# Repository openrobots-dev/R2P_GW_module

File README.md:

R2P GW module
===================

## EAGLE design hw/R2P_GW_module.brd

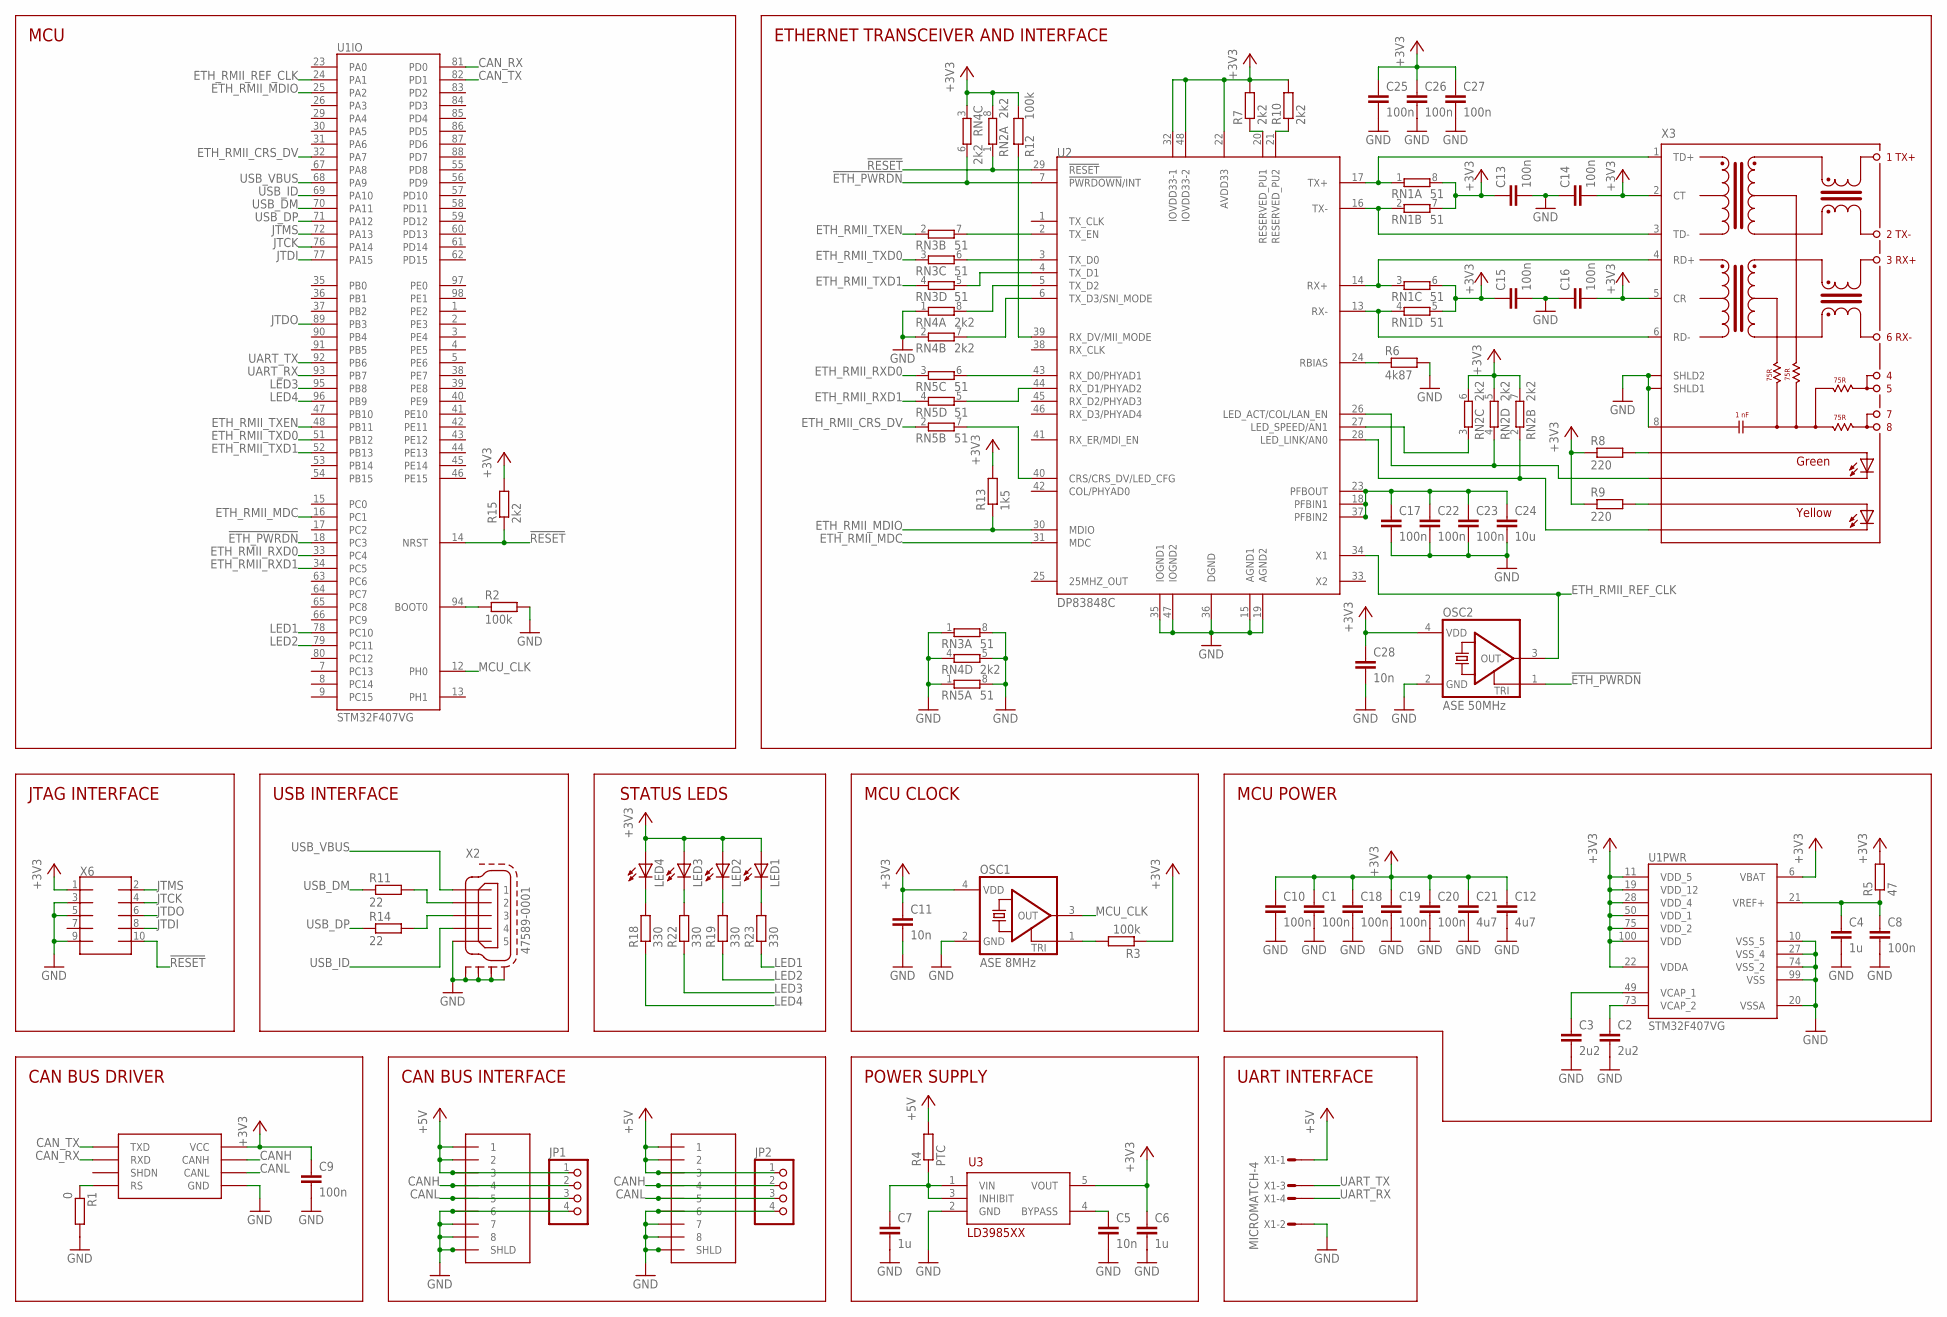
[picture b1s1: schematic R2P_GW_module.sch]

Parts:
C1, C8, C9, C10, C13, C14, C15, C16, C17, C18, C19, C20, C22, C23, C25, C26, C27: 100n; C0603
C2, C3: 2u2; C0805
C4, C6, C7: 1u; C0603
C5, C11, C28: 10n; C0603
C12, C21: 4u7; C0805
C24: 10u; C0805
JP1, JP2: PINHD-1X4; 1X04
LED1, LED2, LED3, LED4: LEDCHIPLED_0805; CHIPLED_0805
OSC1: ASE 8MHz; ASE
OSC2: ASE 50MHz; ASE
R1: 0; R0603
R2, R3, R12: 100k; R0603
R4: PTC; R0603
R5: 47; R0603
R6: 4k87; R0603
R7, R10, R15: 2k2; R0603
R8, R9: 220; R0603
R11, R14: 22; R0603
R13: 1k5; R0603
R18, R19, R22, R23: 330; R0603
RN1, RN3, RN5: 51; CAT16
RN2, RN4: 2k2; CAT16
U1: STM32F407VG; LQFP100
U2: DP83848C; LQFP48
U3: LD3985XX; SOT23-5L
U4: MAX3051; SOT23-8L
X1: MICROMATCH-4
X2: 47589-0001
X3: SI-60062-F
X4, X5: RJ45-43860; 0438600010
X6: FTSH-105

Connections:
!ETH_PWRDN: OSC2.1 (TRI), RN4.6 (2), U1.18 (PC3), U2.7 (!PWRDOWN!/INT)
!RESET: R15.1, RN2.1, U1.14 (NRST), U2.29 (!RESET), X6.10
+3V3: C1.1, C6.1, C9.1, C10.1, C11.1, C12.1, C13.1, C14.2, C15.1, C16.2, C18.1, C19.1, C20.1, C21.1, C25.1, C26.1, C27.1, C28.1, LED1.A, LED2.A, LED3.A, LED4.A, OSC1.4 (VDD), OSC2.4 (VDD), R3.1, R5.2, R7.2, R8.1, R9.1, R10.2, R12.2, R13.2, R15.2, RN1.5 (2), RN1.6 (2), RN1.7 (2), RN1.8 (2), RN2.5 (2), RN2.6 (2), RN2.7 (2), RN2.8 (2), RN4.3 (1), U1.6 (VBAT), U1.11 (VDD_5), U1.19 (VDD_12), U1.22 (VDDA), U1.28 (VDD_4), U1.50 (VDD_1), U1.75 (VDD_2), U1.100 (VDD), U2.22 (AVDD33), U2.32 (IOVDD33-1), U2.48 (IOVDD33-2), U3.5 (VOUT), U4.P$3 (VCC), X3.2 (CT), X3.5 (CR), X6.1
+5V: JP1.1, JP2.1, R4.2, X1.1, X4.P$1 (1), X4.P$2 (2), X4.P$3 (3), X5.P$1 (1), X5.P$2 (2), X5.P$3 (3)
CANH: JP1.2, JP2.2, U4.P$7 (CANH), X4.P$4 (4), X5.P$4 (4)
CANL: JP1.3, JP2.3, U4.P$6 (CANL), X4.P$5 (5), X5.P$5 (5)
CAN_RX: U1.81 (PD0), U4.P$4 (RXD)
CAN_TX: U1.82 (PD1), U4.P$1 (TXD)
ETH_RMII_CRS_DV: RN5.2 (1), U1.32 (PA7)
ETH_RMII_MDC: U1.16 (PC1), U2.31 (MDC)
ETH_RMII_MDIO: R13.1, U1.25 (PA2), U2.30 (MDIO)
ETH_RMII_REF_CLK: OSC2.3 (OUT), U1.24 (PA1), U2.34 (X1)
ETH_RMII_RXD0: RN5.3 (1), U1.33 (PC4)
ETH_RMII_RXD1: RN5.4 (1), U1.34 (PC5)
ETH_RMII_TXD0: RN3.3 (1), U1.51 (PB12)
ETH_RMII_TXD1: RN3.4 (1), U1.52 (PB13)
ETH_RMII_TXEN: RN3.2 (1), U1.48 (PB11)
GND: C1.2, C2.2, C3.2, C4.2, C5.2, C6.2, C7.2, C8.2, C9.2, C10.2, C11.2, C12.2, C13.2, C14.1, C15.2, C16.1, C17.2, C18.2, C19.2, C20.2, C21.2, C22.2, C23.2, C24.2, C25.2, C26.2, C27.2, C28.2, JP1.4, JP2.4, OSC1.2 (GND), OSC2.2 (GND), R1.2, R2.2, R6.2, RN3.1, RN3.8 (2), RN4.1, RN4.2 (1), RN4.4 (1), RN4.5 (2), RN5.1, RN5.8 (2), U1.10 (VSS_5), U1.20 (VSSA), U1.27 (VSS_4), U1.74 (VSS_2), U1.99 (VSS), U2.15 (AGND1), U2.19 (AGND2), U2.35 (IOGND1), U2.36 (DGND), U2.47 (IOGND2), U3.2 (GND), U4.P$2 (GND), X1.2, X2.5, X2.SHLD1, X2.SHLD2, X2.SHLD3, X2.SHLD4, X3.8, X3.SHLD1, X3.SHLD2, X4.P$6 (6), X4.P$7 (7), X4.P$8 (8), X4.P$9 (SHLD), X4.P$10, X5.P$6 (6), X5.P$7 (7), X5.P$8 (8), X5.P$9 (SHLD), X5.P$10, X6.3, X6.5, X6.9
JTCK: U1.76 (PA14), X6.4
JTDI: U1.77 (PA15), X6.8
JTDO: U1.89 (PB3), X6.6
JTMS: U1.72 (PA13), X6.2
LED1: R23.1, U1.78 (PC10)
LED2: R19.1, U1.79 (PC11)
LED3: R22.1, U1.95 (PB8)
LED4: R18.1, U1.96 (PB9)
MCU_CLK: OSC1.3 (OUT), U1.12 (PH0)
unnamed: C4.1, C8.1, R5.1, U1.21 (VREF+)
unnamed: R1.1, U4.P$8 (RS)
unnamed: OSC1.1 (TRI), R3.2
unnamed: C5.1, U3.4 (BYPASS)
unnamed: C7.1, R4.1, U3.1 (VIN), U3.3 (INHIBIT)
unnamed: R6.1, U2.24 (RBIAS)
unnamed: R11.2, X2.2
unnamed: RN1.1, U2.17 (TX+), X3.1 (TD+)
unnamed: RN1.2 (1), U2.16 (TX-), X3.3 (TD-)
unnamed: RN1.3 (1), U2.14 (RX+), X3.4 (RD+)
unnamed: RN1.4 (1), U2.13 (RX-), X3.6 (RD-)
unnamed: R9.2, X3.YA
unnamed: C17.1, C22.1, C23.1, C24.1, U2.18 (PFBIN1), U2.23 (PFBOUT), U2.37 (PFBIN2)
unnamed: LED4.C, R18.2
unnamed: R8.2, X3.GA
unnamed: LED2.C, R19.2
unnamed: RN2.3 (1), U2.27 (LED_SPEED/AN1)
unnamed: LED3.C, R22.2
unnamed: RN3.7 (2), U2.2 (TX_EN)
unnamed: LED1.C, R23.2
unnamed: RN2.2 (1), U2.28 (LED_LINK/AN0), X3.YK
unnamed: RN2.4 (1), U2.26 (LED_ACT/COL/LAN_EN), X3.GK
unnamed: RN3.6 (2), U2.3 (TX_D0)
unnamed: R2.1, U1.94 (BOOT0)
unnamed: R7.1, U2.20 (RESERVED_PU1)
unnamed: R10.1, U2.21 (RESERVED_PU2)
unnamed: RN3.5 (2), U2.4 (TX_D1)
unnamed: RN4.8 (2), U2.5 (TX_D2)
unnamed: RN4.7 (2), U2.6 (TX_D3/SNI_MODE)
unnamed: R14.2, X2.3
unnamed: RN5.6 (2), U2.43 (RX_D0/PHYAD1)
unnamed: R12.1, U2.39 (RX_DV/MII_MODE)
unnamed: RN5.5 (2), U2.44 (RX_D1/PHYAD2)
unnamed: RN5.7 (2), U2.40 (CRS/CRS_DV/LED_CFG)
UART_RX: U1.93 (PB7), X1.4
UART_TX: U1.92 (PB6), X1.3
USB_DM: R11.1, U1.70 (PA11)
USB_DP: R14.1, U1.71 (PA12)
USB_ID: U1.69 (PA10), X2.4
USB_VBUS: U1.68 (PA9), X2.1
VCAP_1: C3.1, U1.49 (VCAP_1)
VCAP_2: C2.1, U1.73 (VCAP_2)

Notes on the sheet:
MCU
POWER SUPPLY
STATUS LEDS
JTAG INTERFACE
CAN BUS INTERFACE
CAN BUS DRIVER
UART INTERFACE
ETHERNET TRANSCEIVER AND INTERFACE
MCU POWER
MCU CLOCK
USB INTERFACE

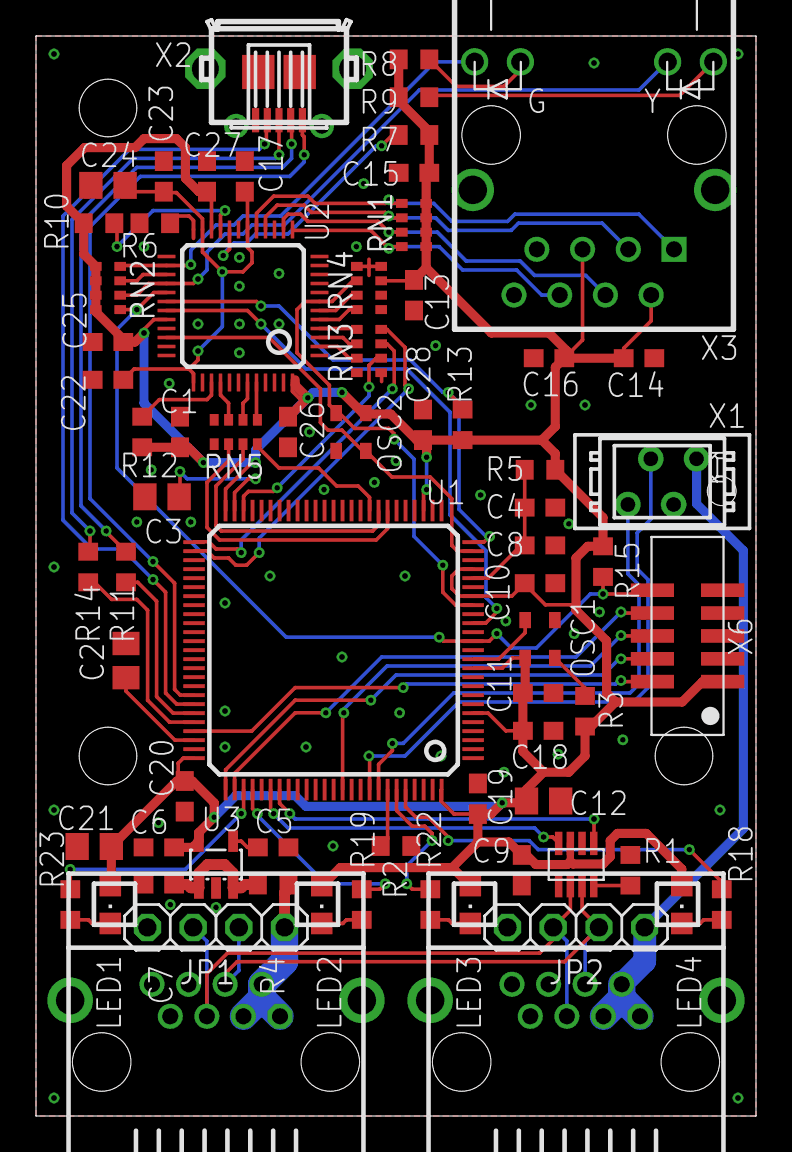
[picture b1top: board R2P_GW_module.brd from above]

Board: 2 copper layers, 40.0 x 60.0 mm, 70 parts (0 on the bottom side), 69 nets.

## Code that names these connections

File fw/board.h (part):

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/*
 * IO pins assignments.
 */
#define LED1_GPIO				GPIOC
#define LED1					10
#define LED2_GPIO				GPIOC
#define LED2					11
#define LED3_GPIO				GPIOB
#define LED3					8
#define LED4_GPIO				GPIOB
#define LED4					9

#define SERIAL_DRIVER           SD1

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 * GPIOA setup:
 *
 * PA0  - PIN0                      (input pullup).
 * PA1  - ETH_RMII_REF_CLK          (alternate 11).
 * PA2  - ETH_RMII_MDIO             (alternate 11).
 * PA3  - PIN3                      (input pullup).
 * PA4  - PIN4                      (input pullup).
 * PA5  - PIN5                      (input pullup).
 * PA6  - PIN6                      (input pullup).
 * PA7  - ETH_RMII_CRS_DV           (alternate 11).
 * PA8  - PIN8                      (input pullup).
 * PA9  - OTG_FS_VBUS               (input pulldown).
 * PA10 - OTG_FS_ID                 (alternate 10).
 * PA11 - OTG_FS_DM                 (alternate 10).
 * PA12 - OTG_FS_DP                 (alternate 10).
 * PA13 - JTMS                      (alternate 0).
 * PA14 - JTCK                      (alternate 0).
 * PA15 - JTDI                      (alternate 0).
 */
#define VAL_GPIOA_MODER             (PIN_MODE_INPUT(GPIOA_PIN0) |           \
                                     PIN_MODE_ALTERNATE(GPIOA_ETH_RMII_REF_CLK) |\
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 * PB0  - PIN0                      (input pullup).
 * PB1  - PIN1                      (input pullup).
 * PB2  - PIN2                      (input pullup).
 * PB3  - JTDO                      (alternate 0).
 * PB4  - JTRST                     (alternate 0).
 * PB5  - PIN5                      (input pullup).
 * PB6  - USART1_TX                 (alternate 7).
 * PB7  - USART1_RX                 (alternate 7).
 * PB8  - LED3                      (output pushpull maximum).
 * PB9  - LED4                      (output pushpull maximum).
 * PB10 - PIN10                     (input pullup).
 * PB11 - ETH_RMII_TX_EN            (alternate 11).
 * PB12 - ETH_RMII_TXD0             (alternate 11).
 * PB13 - ETH_RMII_TXD1             (alternate 11).
 * PB14 - PIN14                     (input pullup).
 * PB15 - PIN15                     (input pullup).
 */
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 * GPIOC setup:
 *
 * PC0  - PIN0                      (input pullup).
 * PC1  - ETH_RMII_MDC              (alternate 11).
 * PC2  - PIN2                      (input pullup).
 * PC3  - ETH_NOT_PWRDN             (output pushpull maximum).
 * PC4  - ETH_RMII_RXD0             (alternate 11).
 * PC5  - ETH_RMII_RXD1             (alternate 11).
 * PC6  - PIN6                      (input pullup).
 * PC7  - PIN7                      (input pullup).
 * PC8  - PIN8                      (input pullup).
 * PC9  - PIN9                      (input pullup).
 * PC10 - LED1                      (output pushpull maximum).
 * PC11 - LED2                      (output pushpull maximum).
 * PC12 - PIN12                     (input pullup).
 * PC13 - PIN13                     (input pullup).
 * PC14 - PIN14                     (input pullup).
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/*
 * GPIOD setup:
 *
 * PD0  - CAN1_RX                   (alternate 9).
 * PD1  - CAN1_TX                   (alternate 9).
 * PD2  - PIN2                      (input pullup).
 * PD3  - PIN3                      (input pullup).
 * PD4  - PIN4                      (input pullup).
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/*
 * GPIOH setup:
 *
 * PH0  - MCU_CLK                   (input pulldown).
 * PH1  - PIN1                      (input pullup).
 * PH2  - PIN2                      (input pullup).
 * PH3  - PIN3                      (input pullup).
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
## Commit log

2012-09-25 Preliminary firmware
    A preliminary firmware was added, based on the STM32F4-DISVOCERY demo.
    It has support (initialization) for:
    _ PAL
    _ MAC RMII
    _ SERIAL
    _ UART
2012-10-14 Schematic reworked
    The schematic was reworked to support a new architecture.
    Andrea Zoppi
2012-10-17 First PCB version almost finished
    Andrea Zoppi
2012-10-17 All the PCB elements routed
    The board has yet to be finally checked.
    Andrea Zoppi
2012-10-18 Minor refinements
    Andrea Zoppi
2012-10-18 Pinout description updated
    Andrea Zoppi
2012-10-26 Added DP83848C datasheet
    Andrea Zoppi
2012-10-26 Minor fixes
    Andrea Zoppi
2012-12-23 Small fixes
    Ethernet CT and CR wired to VDD.
    R12 changed from 100k to 2k2.
    Small changes in traces.
    Andrea Zoppi
2012-12-23 Small updates
    Andrea Zoppi
2013-04-08 Updated blinking led demo
2013-04-11 added blinking led main source
2013-06-18 Fixed LWIP inclusion
2013-06-18 Added LWIP test app
2013-06-19 Added LWIP demo
2013-08-29 blinking_led ok
2013-08-29 lwip_test ok
2013-09-19 added netstream branch
2013-09-19 updated lwip demo
2013-09-19 merged local and remote master branch
2013-09-19 netstreams without LWIP sockets
2013-09-20 clean up
2013-09-25 added missing file
2013-09-25 removed unised files
2013-09-26 added missing files
2013-09-26 restored schematic
2013-09-26 Led, rtcan, and netbg over middleware v2 demo
2013-09-26 fixed demo
2013-09-27 fixed duplicated char
2013-09-27 added transport name
2013-10-05 netdgb almost working
2013-10-05 moved to new GPIO notation
2013-10-06 netdbg demo working
2013-10-11 led blinking
2013-10-22 demo ok
2013-10-22 LWIP test firmware
2013-10-22 cleaned demo
2013-10-25 added pdf
2013-10-25 restored tiltone demo
2013-11-21 small fixies
2013-11-21 disabled unused peripherals
2013-11-22 hardware test firmware
2013-11-27 small fixes
2013-12-12 added board makefile
2013-12-12 moved to HSI
2013-12-12 restored eagle project file
2013-12-12 rostopic list working but not subscribing
2013-12-12 added missing board makefile
2013-12-12 moved to new template parameters
2013-12-12 removed led pub
2013-12-16 fixed timeout
2013-12-16 fixed ip address
2014-01-09 updated to mw v2
2014-02-12 up to date
2014-02-26 working on odometry node
2014-03-06 small fix
2014-03-06 gw ok
2014-03-06 added launch files
2014-03-11 SetPoint done
2014-03-14 quadrivio firmware
2014-03-19 fixed paths
2014-04-10 fixed encoder topics
2014-04-10 fixed for chibios 2.6
2014-04-15 updated for chibi 2.6
2014-06-30 restored lwip demo
2014-07-03 cleaned demo code
2014-07-03 bugfix
2014-07-03 updated to new chibios release
2014-07-04 updated to new led subscriber
2014-07-08 demo setup
2014-07-29 working on demo
2014-10-20 added odometry
2015-03-09 Added missing uros handlers file

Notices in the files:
fw/board.h:
ChibiOS/RT - Copyright (C) 2006,2007,2008,2009,2010,
2011,2012 Giovanni Di Sirio.
